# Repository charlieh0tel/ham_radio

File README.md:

# AI6KG's Amateur Radio git Repository

## Amateur Radio Web Tools

Various web tools including:

- Antenna Matching
- Improved Sherwood Receiver UI

are hosted here:

&nbsp;&nbsp;[https://charlieh0tel.github.io/ham_radio/](https://charlieh0tel.github.io/ham_radio/)

## Other Repos of Amateur Interest

Most of the major projects live in their own repos.

### ASL DMR Bridge

&nbsp;&nbsp;[https://github.com/charlieh0tel/asl-dmr-bridge](https://github.com/charlieh0tel/asl-dmr-bridge)

### Endfed -- "Random" Wire Length Picker

&nbsp;&nbsp;[https://charlieh0tel.github.io/endfed/](https://charlieh0tel.github.io/endfed/)
&nbsp;&nbsp;[https://github.com/charlieh0tel/endfed](https://github.com/charlieh0tel/endfed)

### Tamago Awadateki 卵泡立て器 -- Eggbeater Antenna Design Tool

&nbsp;&nbsp;[https://charlieh0tel.github.io/tamago/](https://charlieh0tel.github.io/tamago/)
&nbsp;&nbsp;[https://github.com/charlieh0tel/tamago](https://github.com/charlieh0tel/tamago)

### Soft SINAD meter

&nbsp;&nbsp;[https://github.com/charlieh0tel/sinad_meter.git](https://github.com/charlieh0tel/sinad_meter.git)

### Rotary Club RDF Framework

&nbsp;&nbsp;[https://github.com/charlieh0tel/rotaryclub.git](https://github.com/charlieh0tel/rotaryclub.git)

## Et Al

The remainder of the repo is various bits and bobs, of which, most is
only useful to AI6KG.

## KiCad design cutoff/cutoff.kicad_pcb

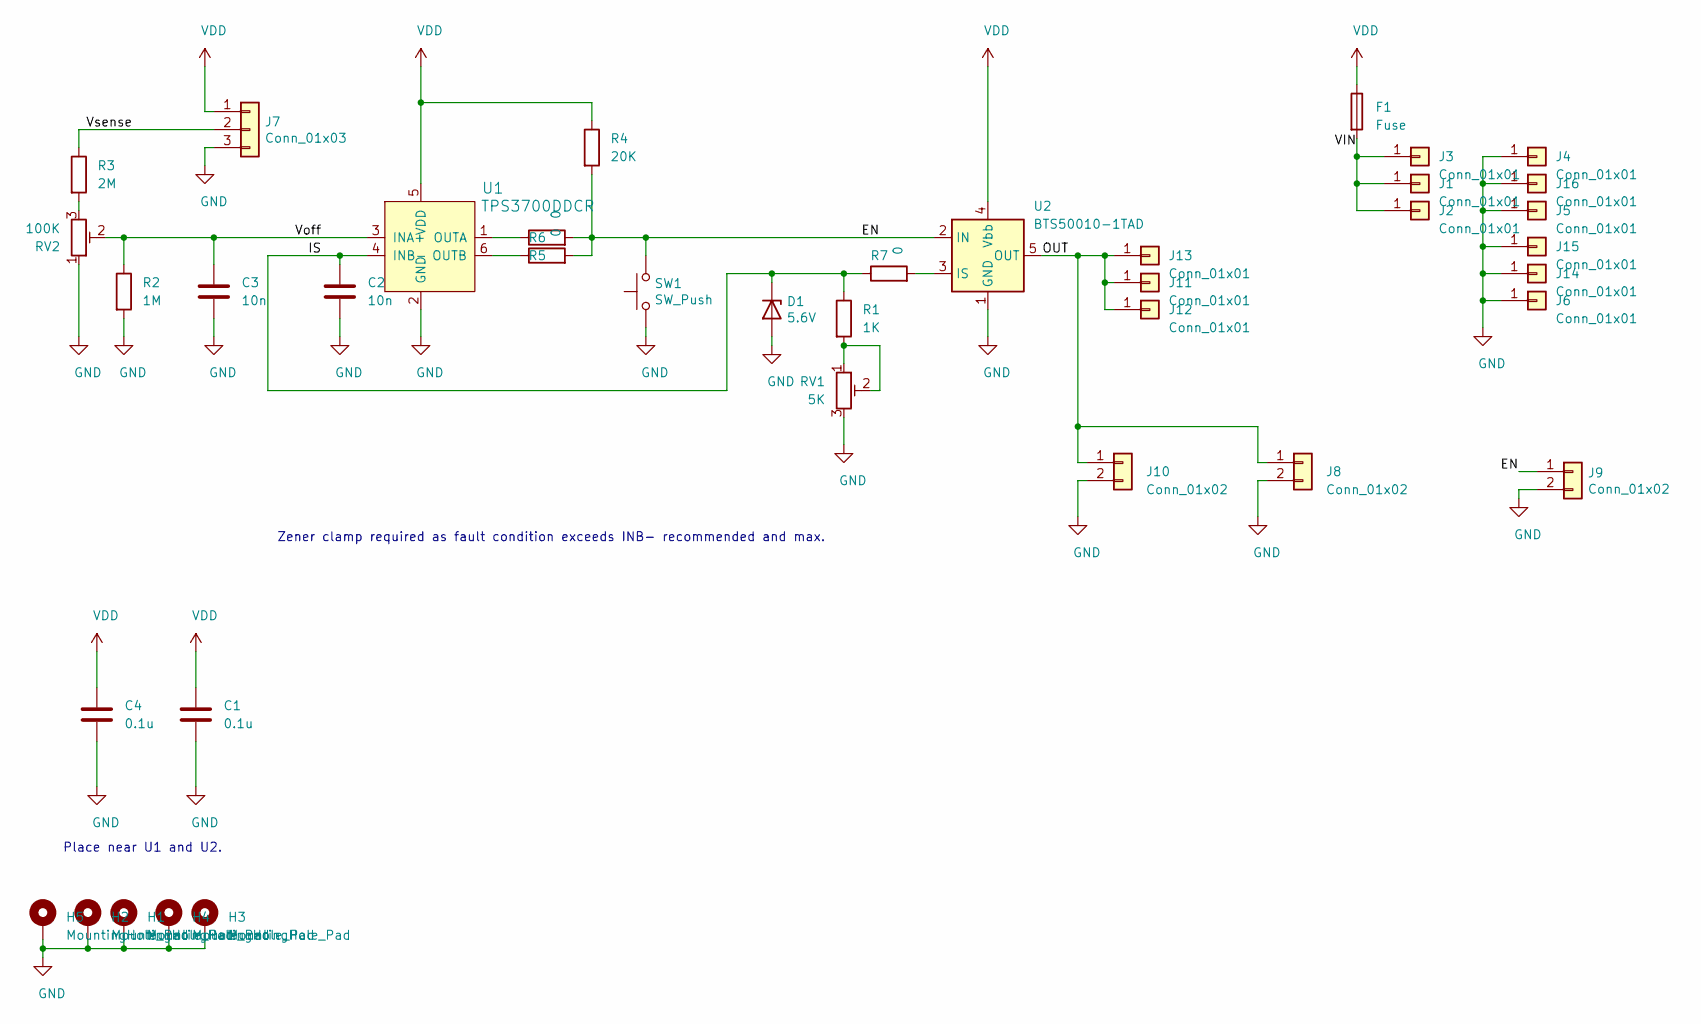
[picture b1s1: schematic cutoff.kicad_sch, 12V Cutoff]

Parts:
C1, C4: 0.1u; C_0805_2012Metric_Pad1.18x1.45mm_HandSolder
C2, C3: 10n; C_0805_2012Metric_Pad1.18x1.45mm_HandSolder
D1: 5.6V; D_SOD-123
F1: Fuse; Fuseholder_Blade_Mini_Keystone_3568
H1, H2, H3, H4, H5: MountingHole_Pad; MountingHole_3.2mm_M3_Pad
J1, J2, J3, J4, J5, J6, J11, J12, J13, J14, J15, J16: Conn_01x01; SolderWire-2.5sqmm_1x01_D2.4mm_OD4.4mm
J7: Conn_01x03; PinHeader_1x03_P2.54mm_Vertical
J8, J10: Conn_01x02; 45A-VERT-PAIR
J9: Conn_01x02; PinHeader_1x02_P2.54mm_Vertical
R1: 1K; R_0805_2012Metric_Pad1.20x1.40mm_HandSolder
R2: 1M; R_0805_2012Metric_Pad1.20x1.40mm_HandSolder
R3: 2M; R_0805_2012Metric_Pad1.20x1.40mm_HandSolder
R4: 20K; R_0805_2012Metric_Pad1.20x1.40mm_HandSolder
R5, R6, R7: 0; R_0805_2012Metric_Pad1.20x1.40mm_HandSolder
RV1: 5K; Potentiometer_Bourns_3224X_Vertical
RV2: 100K; Potentiometer_Bourns_3224X_Vertical
SW1: SW_Push; SW_SPST_PTS810
U1: TPS3700DDCR; SOT-23-6; MPN TPS3700DDCR; Digi-Key_PN 296-30395-1-ND
U2: BTS50010-1TAD; TO-263-7_TabPin4

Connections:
/EN: J9.1, R4.2, R5.2, R6.2, SW1.2, U2.2 (IN)
/IS: C2.1, D1.1 (K), R1.1, R7.1, U1.4 (INB-)
/OUT: J8.1, J10.1, J11.1, J12.1, J13.1, U2.5 (OUT), U2.6 (OUT), U2.7 (OUT)
/VIN: F1.2, J1.1, J2.1, J3.1
/Voff: C3.1, R2.1, RV2.2, U1.3 (INA+)
/Vsense: J7.2, R3.1
GND: C1.2, C2.2, C3.2, C4.2, D1.2 (A), H1.1, H2.1, H3.1, H4.1, H5.1, J4.1, J5.1, J6.1, J7.3, J8.2, J9.2, J10.2, J14.1, J15.1, J16.1, R2.2, RV1.3, RV2.1, SW1.1, U1.2 (GND), U2.1 (GND)
unnamed: R1.2, RV1.1, RV1.2
unnamed: R3.2, RV2.3
unnamed: R6.1, U1.1 (OUTA)
unnamed: R5.1, U1.6 (OUTB)
unnamed: R7.2, U2.3 (IS)
VDD: C1.1, C4.1, F1.1, J7.1, R4.1, U1.5 (VDD), U2.4 (Vbb)

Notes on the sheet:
Place near U1 and U2.
Zener clamp required as fault condition exceeds INB- recommended and max.

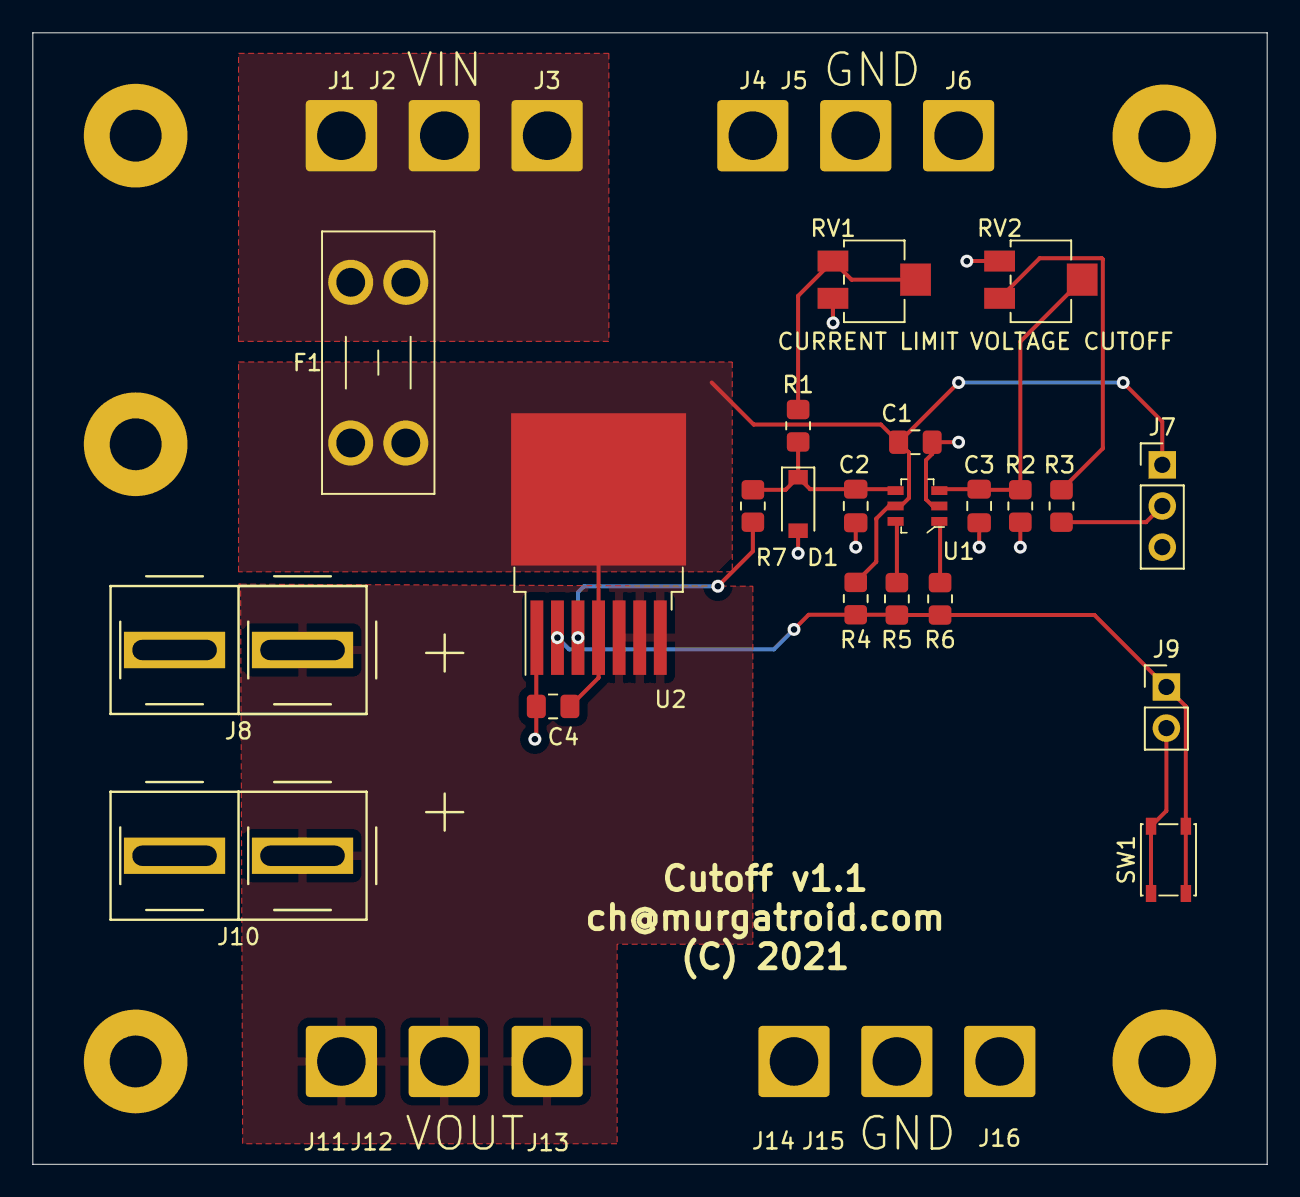
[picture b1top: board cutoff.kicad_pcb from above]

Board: 2 copper layers, 76.2 x 69.9 mm, 39 parts (0 on the bottom side), 13 nets.

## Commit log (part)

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2021-01-23 Mo betta packet
2021-01-25 Fixes input for 9600 baud left.
2021-01-25 Moves stuff into draws specific directory.
2021-01-25 Adds gpio_set.sh for DRAWS
2021-02-04 Settings for TX-790 9600 baud inputs.
    ======= DRAWS
    ===== ALSA Controls for Radio Transmit =====
    LO Driver Gain L:[7.00dB] R:[7.00dB]
    PCM L:[0.00dB] R:[0.00dB]
    DAC Playback PT L:[P3] R:[P3]
    LO Playback CM [1.65V]
2021-02-04 For TX-790, bump input gain to +16 dB. May be too much.
    ======= DRAWS
    ===== ALSA Controls for Radio Transmit =====
    LO Driver Gain L:[7.00dB] R:[7.00dB]
    PCM L:[0.00dB] R:[0.00dB]
    DAC Playback PT L:[P3] R:[P3]
    LO Playback CM [1.65V]
2021-02-05 Bump input gain to +10 dB
2021-02-05 Adds ft991 ax25 direwolf config
2021-02-07 DRAWS asound state
2021-02-07 some reorg; add pirim asound state
2021-02-07 update pirim asound state
2021-02-13 svlink for deviation calibration with RTL sdr.
2021-02-15 initial
2021-02-16 Released board (aef0a407e).
2021-02-19 consolidate aprs stuff into packet directory.
2021-02-19 digipeater conf
2021-03-15 inverted delta loop models
2022-06-24 gnuplot file
2023-02-12 cleanup
2023-02-12 Update for HiDPI screen.
2023-02-12 Don't mess with default window size. Embiggen the fonts for HiDPI.
2023-02-16 Fix busted push
2023-03-20 Janky script to create KML from ULS records.
2023-03-29 Useful rtlsdr blacklist.
2024-09-24 New tuning for TK-790.
2024-09-29 packet setup on edamame
2024-10-09 get rid of sudo
2024-10-13 checkpoint
2024-10-14 switch to csv, json from dataframes is carcrash.
2024-10-14 remove accidental checkin
2024-10-14 add mean, sd to plots
2024-10-14 Cleanup plots.
2024-10-14 Revert "prettier plots"
    This reverts commit aca2b54b82dcd7e75d90c665d35e5770d8c598f4.
    Something is busted.
2024-10-14 prettier plots that work
2024-10-14 gitignores
2024-10-14 better y axis
2024-10-15 Allow setting y divisions; remove old calibration results
2024-10-21 Remove older programs
2024-10-21 Updates .gitignore
2025-02-01 write freqs and clean up read freqs
2025-02-01 new codeplug with my test freqs
2025-02-01 orig
2025-02-03 16 test freqs
2025-02-03 Leave stock test frequencies at top for alignment.
2025-02-16 latest
2025-02-18 Increases number of samples; adds moving average filter for numerical dispaly.
2025-02-18 * Speeds up plotting.
    * Optionally, allows enabling of channel 1 ouput to it can be looped
    back for development.
    * autopep8
2025-03-11 Cleans up venv set up.
2025-04-28 Refactored and added support for PortAudio devices.
    Major clean up.
2025-04-28 Moves sinad_meter to its own repo.
2025-12-27 Hairpin now respects the antenna reactance.
    Don't allow non-physical tap point for gamma match.
2025-12-27 Use mathjs complex.
2025-12-27 Switch to Nelder-Mead for auto-tuning.
2025-12-27 Minor cleanup
2025-12-27 Makes the Smith chart easier to see.
2025-12-28 Add author attribution and footer with license/repo links
2025-12-28 Improve physical arrangement diagrams
    - Redraw gamma match with cleaner coax feed style
    - Split beta match driven element to show gap clearly
    - Add λ/2 and λ/4 labels to antenna segments
    - Rename Hairpin (Beta) to Beta (Hairpin)
    - Move capacitor label below symbol
2025-12-28 Use standard capacitor symbol in gamma match diagram
2025-12-28 Add optional physical parameters (frequency, element diameter)
    Shows capacitor value in pF for gamma match and element
    shortening in mm for beta match when parameters are provided.
2025-12-28 Add tap point distance calculation for gamma match
    Shows physical distance from center in mm when frequency is entered.
2025-12-28 Default element diameter to 2mm
2025-12-28 Allow zero shortening in beta match
2025-12-28 Fix layout shift by using (L)/(C) for reactance labels
2025-12-28 Add mobile responsive layout and tooltips
2025-12-28 Increase Smith chart size from 440px to 520px
2025-12-28 Refactor: extract constants, add input helpers, clean up
    URL_KEYS, C_SPEED constants; setNum/setStr helpers; getSWRClass pure fn
2025-12-28 Add MODES constant, replace mode string literals
2025-12-28 Refactor: production React, ControlPanel component, accessibility, cleanup
2025-12-28 Extract GammaDiagram and HairpinDiagram components
2025-12-28 Fix Smith chart aspect ratio on mobile with viewBox and aspect-ratio
2025-12-28 Add isGamma helper, consolidate print CSS
2025-12-28 gitignore
2025-12-28 Fix Smith chart path discontinuities and consolidate constants
    - Fix shunt paths to start exactly at previous transformation point
    - Add SHUNT_X_START constant for path animation starting reactance
    - Add PATH_R_MAX/PATH_X_MAX for consistent path filtering
    - Add SHUNT_X_MIN, SWR_MAX, SWR_THRESHOLDS constants
    - Add TUNE_BOUNDS for auto-tune parameter limits
    - Derive initial guesses from bounds instead of magic numbers
2025-12-28 Add full complex impedance labels to all Smith chart points
2025-12-28 Prevent Smith chart from being squished by flex
2025-12-28 Auto-tune on initial page load when no URL params
2025-12-28 Fix shunt path arcs using susceptance interpolation
    Linear interpolation in reactance space bunched points near the start,
    making long arcs appear as two line segments. Interpolating in
    susceptance (B = -1/X) space produces evenly-spaced points along the
    constant-G circles.
2025-12-31 wav splitter
2026-01-06 Use SVG arc commands for shunt paths on Smith chart
    Replace polyline approximations with true circular arcs for
    constant-G (conductance) circle paths. Fixes flat spots that
    appeared on large arcs due to insufficient line segments.
2026-01-06 Refactor shunt arc calculation into shared helper
    - Extract calcShuntArc() to compute arc path and arrow angle
    - Calculate arrow angle from circle geometry instead of polyline
    - Remove vestigial polyline computation for shunt paths
    - Remove unused SHUNT_X_START and PATH_X_MAX constants
    - Net reduction of ~45 lines
2026-01-06 Add Z factory function for impedance objects with format methods
    Replaces separate r,x parameters with Z(r,x) factory that returns
    impedance objects with .format() and .formatLabel() methods attached.
2026-01-09 Reorganize code sections and simplify conditionals
2026-02-23 add CLAUDE.md project instructions
2026-02-23 Refactor into per-mode objects, add OCFD enhancements, scale up UI
    - Consolidate all mode-specific code into gammaMode/hairpinMode/ocfdMode
    objects with uniform interface (calc, tune, Controls, Diagram, etc.)
    - Remove scattered MODE_DEFS, standalone hooks, tune functions, and
    mode-specific components in favor of MODE_MAP dispatch
    - Main component now has zero mode branching
    - Add per-mode presets (gamma/hairpin antenna presets, OCFD scenarios)
2026-02-24 Add IEMF dipole impedance, lossy ground, and dipole calculator UI
    Replace fixed 73.1+j42.5 Ω with induced EMF method (Balanis Eqs. 8-60a/b)
    for wire-diameter-dependent feedpoint impedance. Add Fresnel reflection
    for lossy ground types (perfect/sea/wet/average/dry/city/free-space).
    Restructure OCFD controls with a dedicated dipole calculator panel
    including freq, wire diameter, height, and ground type inputs. Fix
    diagram feed position at 50% offset and clamp extreme impedance display.
2026-02-24 Redraw gamma match diagram with correct coax topology
    Show shield and center conductor as distinct elements: shield (gray wire)
    from element center up to coax, center conductor exits to series cap then
    gamma rod. Cap on left, gamma rod and tap on right. Coax drawn with
    parallel shield walls, center conductor, and top ellipse cross-section.
2026-02-24 Shared dipole calculator, resonant length, OCFD enhancements
    - Extract DipoleCalculator as shared collapsible component across
    all modes (gamma, hairpin, OCFD) with wire diameter, height, and
    ground type inputs
    - Add calcDipoleResonant: bisection to find resonant dipole length
    (X_in=0) with bracket validation fallback
    - Update calcDipoleOverGround to use resonant length for both self
2026-02-24 Fix bugs from codebase audit, add OCFD and math unit tests
    Accessibility: focus-visible outlines, keyboard-accessible calculator header.
    Math: guard IEMF div-by-zero, fix Si/Ci asymptotic g(x), correct hairpin
    Z₀ formula (276·log10(λ/d)), fix Smith chart arc large-arc-flag.
    React: guard clipboard API, optimize handleAutoTune dependencies.
    Tests: 20 new tests — OCFD functional (12.1–12.11), core math (13.1–13.9).
2026-02-24 Use Schelkunoff Z₀ for hairpin shortening estimate
    Replace 276·log₁₀(λ/d) with 120·(ln(2h/a) − 1) for the antenna
    element characteristic impedance in the hairpin shortening display.
    The Schelkunoff average Z₀ is more accurate for this purpose.
2026-02-24 OCFD presets compute impedance from dipole calculator
    Non-free-space OCFD presets (λ/2 AGL, λ/4 AGL) now dynamically compute
    impedance using calcDipoleOverGround instead of hardcoded values. Presets
    are disabled when no frequency is entered. Clicking a computed preset
    opens the dipole calculator; static presets close it. Mode switching
    resets calculator state. Added (i) info popover with references, Apply
    button dims when already applied, and panel numbering for OCFD controls.
2026-03-28 sherwood viewer
2026-03-28 add diagonal to chart
2026-03-28 fix diagonal
2026-03-28 feat: add date, footnotes, LO noise chart, click highlight, meta tags, credit
2026-03-28 feat: improve chart highlighting
2026-03-28 feat: change legend layout
2026-03-28 feat: multi-select row comparison with clear button
2026-03-28 fix: bar chart highlight consistent with scatter plots
2026-03-28 fix: show all bar chart labels, add units to title, increase chart height
2026-03-28 feat: UI/JS improvements and model name cleanup
    - Fix column resize on sort: use fixed-width arrow span
    - Sort only rebuilds table, not charts
    - Move prefix text before brand name to end of model name
    - Extract KNOWN_BRANDS constant (DRY)
2026-03-29 feat: improve mobile responsiveness
    - Stack controls vertically below 700px
    - Single-column stats below 420px
    - Smooth touch scrolling on table
    - Smaller header title on narrow screens
2026-05-22 feat: add docs landing page linking to tools
2026-06-27 feat: eggbeater antenna dimension generator with nec2c tuning
2026-06-27 feat: frequency sweep reporting 2:1 VSWR bandwidth
2026-06-27 feat: select polarization sense (rhcp/lhcp) with nec2c verification
2026-06-27 feat: optimize reflector spacing and droop for best match
2026-06-27 feat: refresh satellite design deliverables with optimized reflector and bandwidths
2026-06-27 feat: add finite radial-wire reflector option
2026-06-27 feat: add quarter-wave matching transformer to cut sheet
2026-06-27 feat: spec-driven HTML performance plots and satellite_pair.json deliverable
2026-06-27 feat: add generated performance plot page for the satellite pair
2026-06-27 feat: show input spec and cut list on the plot page; share cut-sheet formatter via report.py
2026-06-29 feat: optimizer is a spec->spec transform with provenance; add --emit-spec
2026-06-29 feat: restore sat-pair lineage (authored input -> optimized spec with provenance)
2026-06-29 feat: brief metric definitions under the table and a note under each chart
2026-06-29 docs: add TODO list
2026-06-30 feat: add worst-case coverage-gain figure of merit
2026-06-30 feat: optimize radial count (fewest meeting AR/VSWR); sat pair to 3 radials
2026-06-30 docs: add az-el plot TODO
2026-06-30 docs: drop completed TODO items
2026-06-30 feat: square and squircle loop shapes
    loop_shape selects the loop outline: circle (default), square, or squircle
    (a square with radiused corners -- four straight sides joined by
    quarter-circle arcs, radius set by corner_radius_wl). Loop perimeter is held
    fixed across shapes; non-circular outlines resample to equal-length NEC
    segments with the feed on the bottom side. The cut sheet and result JSON
    report the shape, corner radius, and across dimension (diameter or side/width).
2026-06-30 docs: add squircle-loop satellite pair example

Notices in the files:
cutoff/cutoff.kicad_pcb:
(C) 2021
